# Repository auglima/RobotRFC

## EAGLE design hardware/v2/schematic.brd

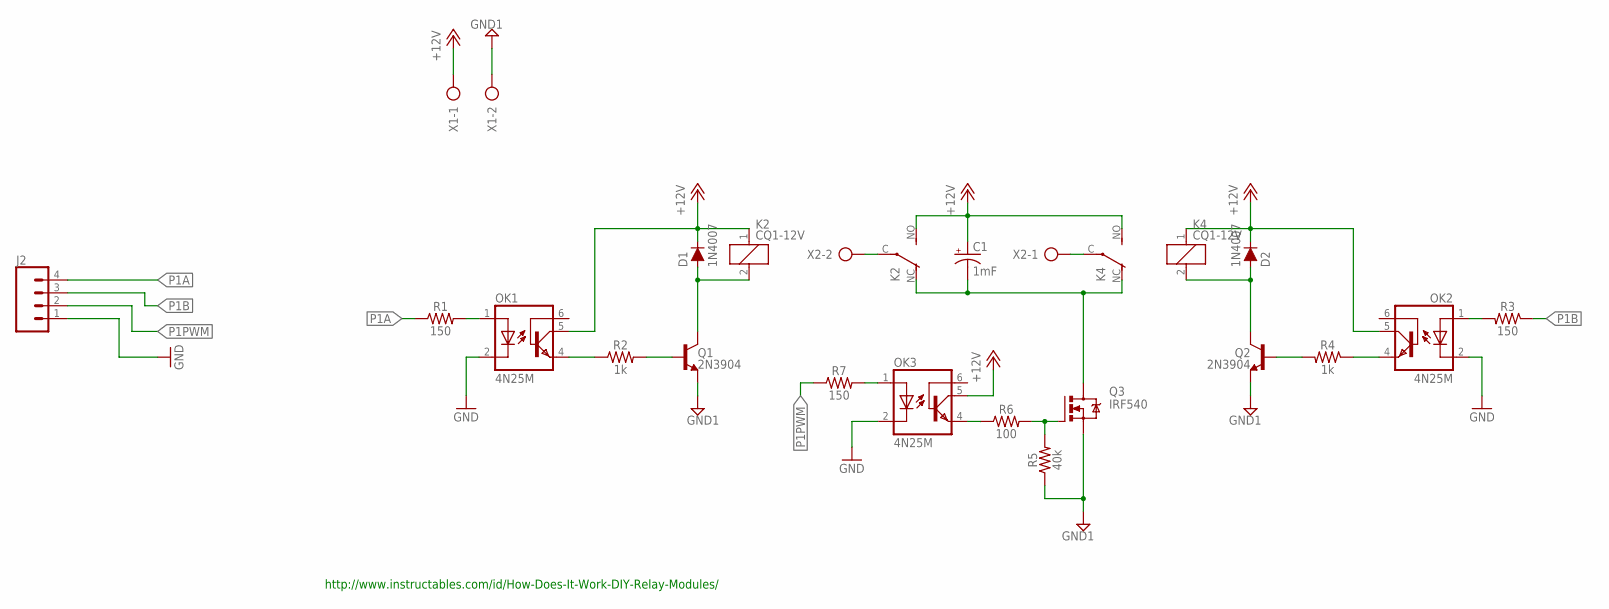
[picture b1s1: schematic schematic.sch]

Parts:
C1: 1mF; CPOL-RADIAL-5MM-10MM
D1, D2: 1N4007; DIODE-1N4001
J2: CONN_04LOCK_LONGPADS; 1X04_LOCK_LONGPADS
K2, K4: CQ1-12V; CQ1
OK1, OK2, OK3: 4N25M; DIL06
Q1, Q2: 2N3904; TO-92
Q3: IRF540; TO220BV
R1, R3, R7: 150; AXIAL-0.3
R2, R4: 1k; AXIAL-0.3
R5: 40k; AXIAL-0.3
R6: 100; AXIAL-0.3
X1, X2: AK300/2

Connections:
+12V: C1.+, D1.C, D2.C, K2.1, K2.NO (S), K4.1, K4.NO (S), OK1.5 (COL), OK2.5 (COL), OK3.5 (COL), X1.1
GND: J2.1, OK1.2 (C), OK2.2 (C), OK3.2 (C)
GND1: Q1.1 (E), Q2.1 (E), Q3.S, R5.P$1 (1), X1.2
unnamed: Q1.2 (B), R2.P$2 (2)
unnamed: K4.C, X2.1
unnamed: OK1.1 (A), R1.P$2 (2)
unnamed: K2.C, X2.2
unnamed: D1.A, K2.2, Q1.3 (C)
unnamed: OK2.1 (A), R3.P$2 (2)
unnamed: OK1.4 (EMI), R2.P$1 (1)
unnamed: D2.A, K4.2, Q2.3 (C)
unnamed: OK2.4 (EMI), R4.P$1 (1)
unnamed: Q2.2 (B), R4.P$2 (2)
unnamed: C1.-, K2.NC (O), K4.NC (O), Q3.D
unnamed: OK3.4 (EMI), R6.P$1 (1)
unnamed: Q3.G, R5.P$2 (2), R6.P$2 (2)
unnamed: OK3.1 (A), R7.P$2 (2)
P1A: J2.4, R1.P$1 (1)
P1B: J2.3, R3.P$1 (1)
P1PWM: J2.2, R7.P$1 (1)

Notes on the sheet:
http://www.instructables.com/id/How-Does-It-Work-DIY-Relay-Modules/

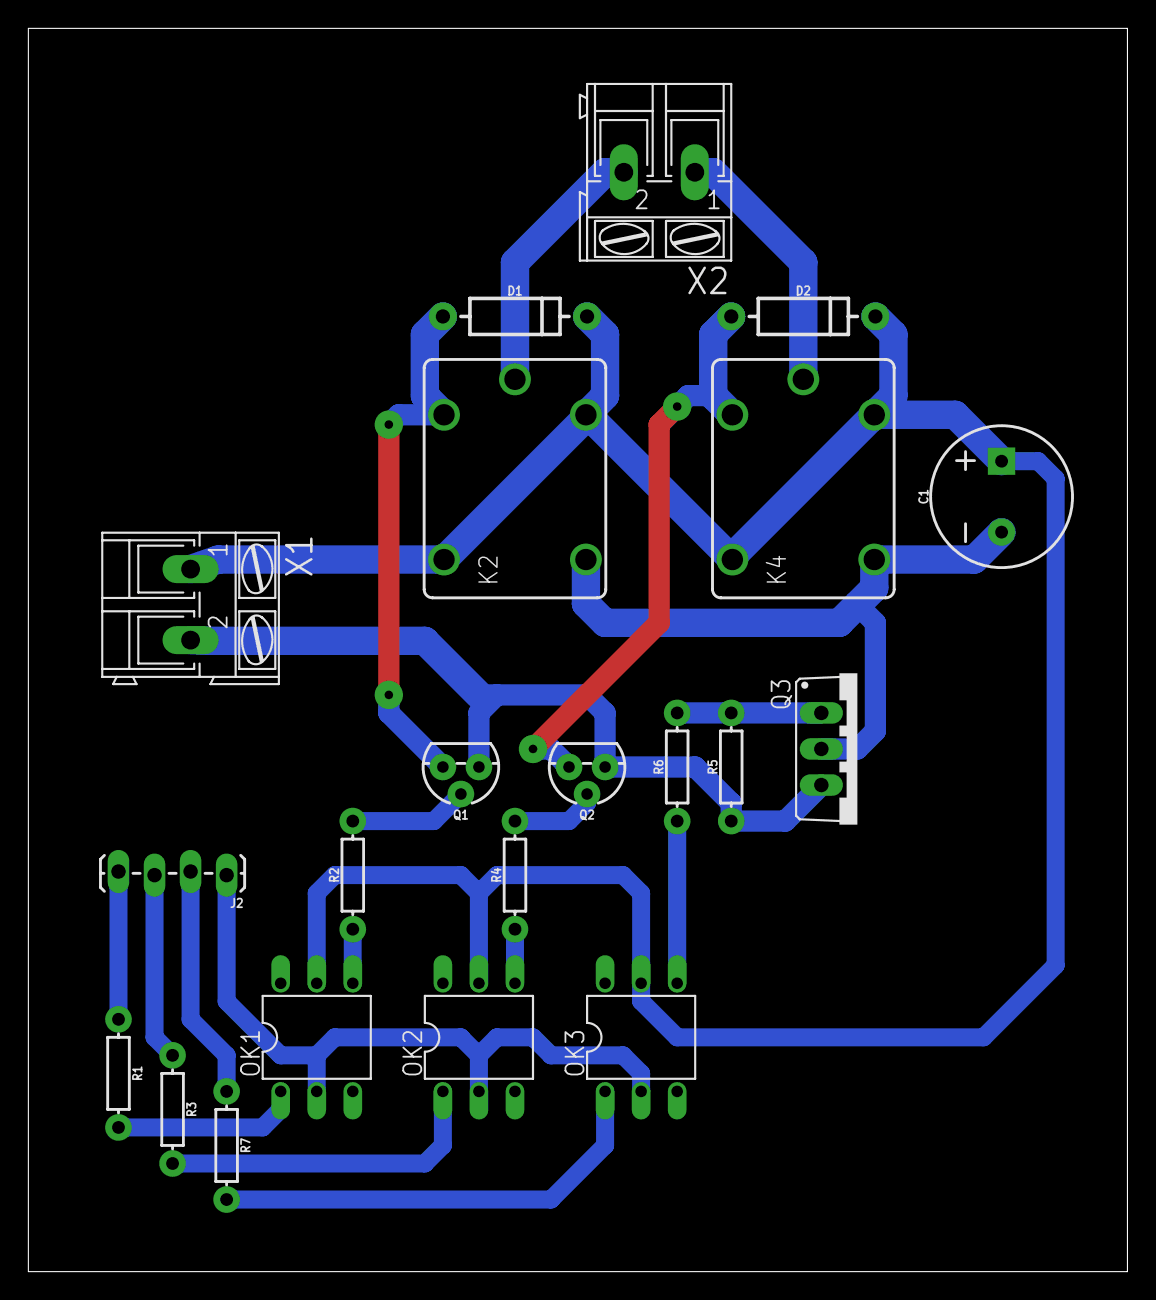
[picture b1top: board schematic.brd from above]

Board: 2 copper layers, 77.5 x 87.6 mm, 21 parts (0 on the bottom side), 20 nets.

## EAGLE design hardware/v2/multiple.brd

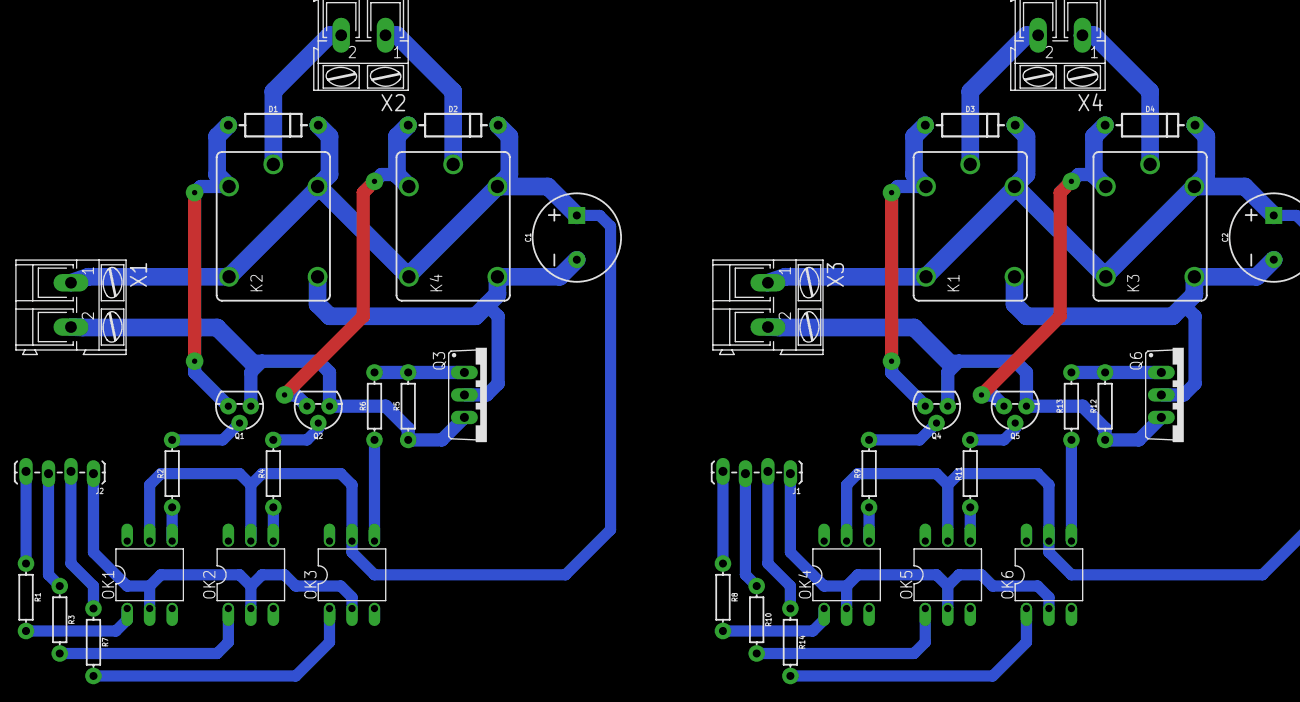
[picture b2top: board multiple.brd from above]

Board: 2 copper layers, 42 parts (0 on the bottom side), 40 nets.

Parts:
C1, C2: 1mF; CPOL-RADIAL-5MM-10MM
D1, D2, D3, D4: 1N4007; DIODE-1N4001
J1, J2: 1X04_LOCK_LONGPADS
K1, K2, K3, K4: CQ1-12V; CQ1
OK1, OK2, OK3, OK4, OK5, OK6: 4N25M; DIL06
Q1, Q2, Q4, Q5: 2N3904; TO-92
Q3, Q6: IRF540; TO220BV
R1, R3, R7, R8, R10, R14: 150; AXIAL-0.3
R2, R4, R9, R11: 1k; AXIAL-0.3
R5, R12: 40k; AXIAL-0.3
R6, R13: 100; AXIAL-0.3
X1, X2, X3, X4: AK300/2

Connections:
+12V: C1.+, D1.C, D2.C, K2.1, K2.NO, K4.1, K4.NO, OK1.5, OK2.5, OK3.5, X1.1
+12V1: C2.+, D3.C, D4.C, K1.1, K1.NO, K3.1, K3.NO, OK4.5, OK5.5, OK6.5, X3.1
GND: J2.1, OK1.2, OK2.2, OK3.2
GND1: Q1.1, Q2.1, Q3.S, R5.P$1, X1.2
GND2: Q4.1, Q5.1, Q6.S, R12.P$1, X3.2
GND3: J1.1, OK4.2, OK5.2, OK6.2
unnamed: Q1.2, R2.P$2
unnamed: K4.C, X2.1
unnamed: OK1.1, R1.P$2
unnamed: K2.C, X2.2
unnamed: D1.A, K2.2, Q1.3
unnamed: OK2.1, R3.P$2
unnamed: OK1.4, R2.P$1
unnamed: D2.A, K4.2, Q2.3
unnamed: OK2.4, R4.P$1
unnamed: Q2.2, R4.P$2
unnamed: C1.-, K2.NC, K4.NC, Q3.D
unnamed: OK3.4, R6.P$1
unnamed: Q3.G, R5.P$2, R6.P$2
unnamed: OK4.1, R8.P$2
unnamed: OK3.1, R7.P$2
unnamed: D3.A, K1.2, Q4.3
unnamed: OK4.4, R9.P$1
unnamed: Q4.2, R9.P$2
unnamed: OK5.1, R10.P$2
unnamed: D4.A, K3.2, Q5.3
unnamed: OK5.4, R11.P$1
unnamed: Q5.2, R11.P$2
unnamed: C2.-, K1.NC, K3.NC, Q6.D
unnamed: OK6.4, R13.P$1
unnamed: Q6.G, R12.P$2, R13.P$2
unnamed: OK6.1, R14.P$2
unnamed: K3.C, X4.1
unnamed: K1.C, X4.2
P1A: J2.4, R1.P$1
P1A1: J1.4, R8.P$1
P1B: J2.3, R3.P$1
P1B1: J1.3, R10.P$1
P1PWM: J2.2, R7.P$1
P1PWM1: J1.2, R14.P$1

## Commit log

2018-05-24 add project
2018-05-25 update!

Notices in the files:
parts and their libraries:
SparkFun-Capacitors: Licensing: Creative Commons ShareAlike 4.0 International - https://creativecommons.org/licenses/by-sa/4.0
